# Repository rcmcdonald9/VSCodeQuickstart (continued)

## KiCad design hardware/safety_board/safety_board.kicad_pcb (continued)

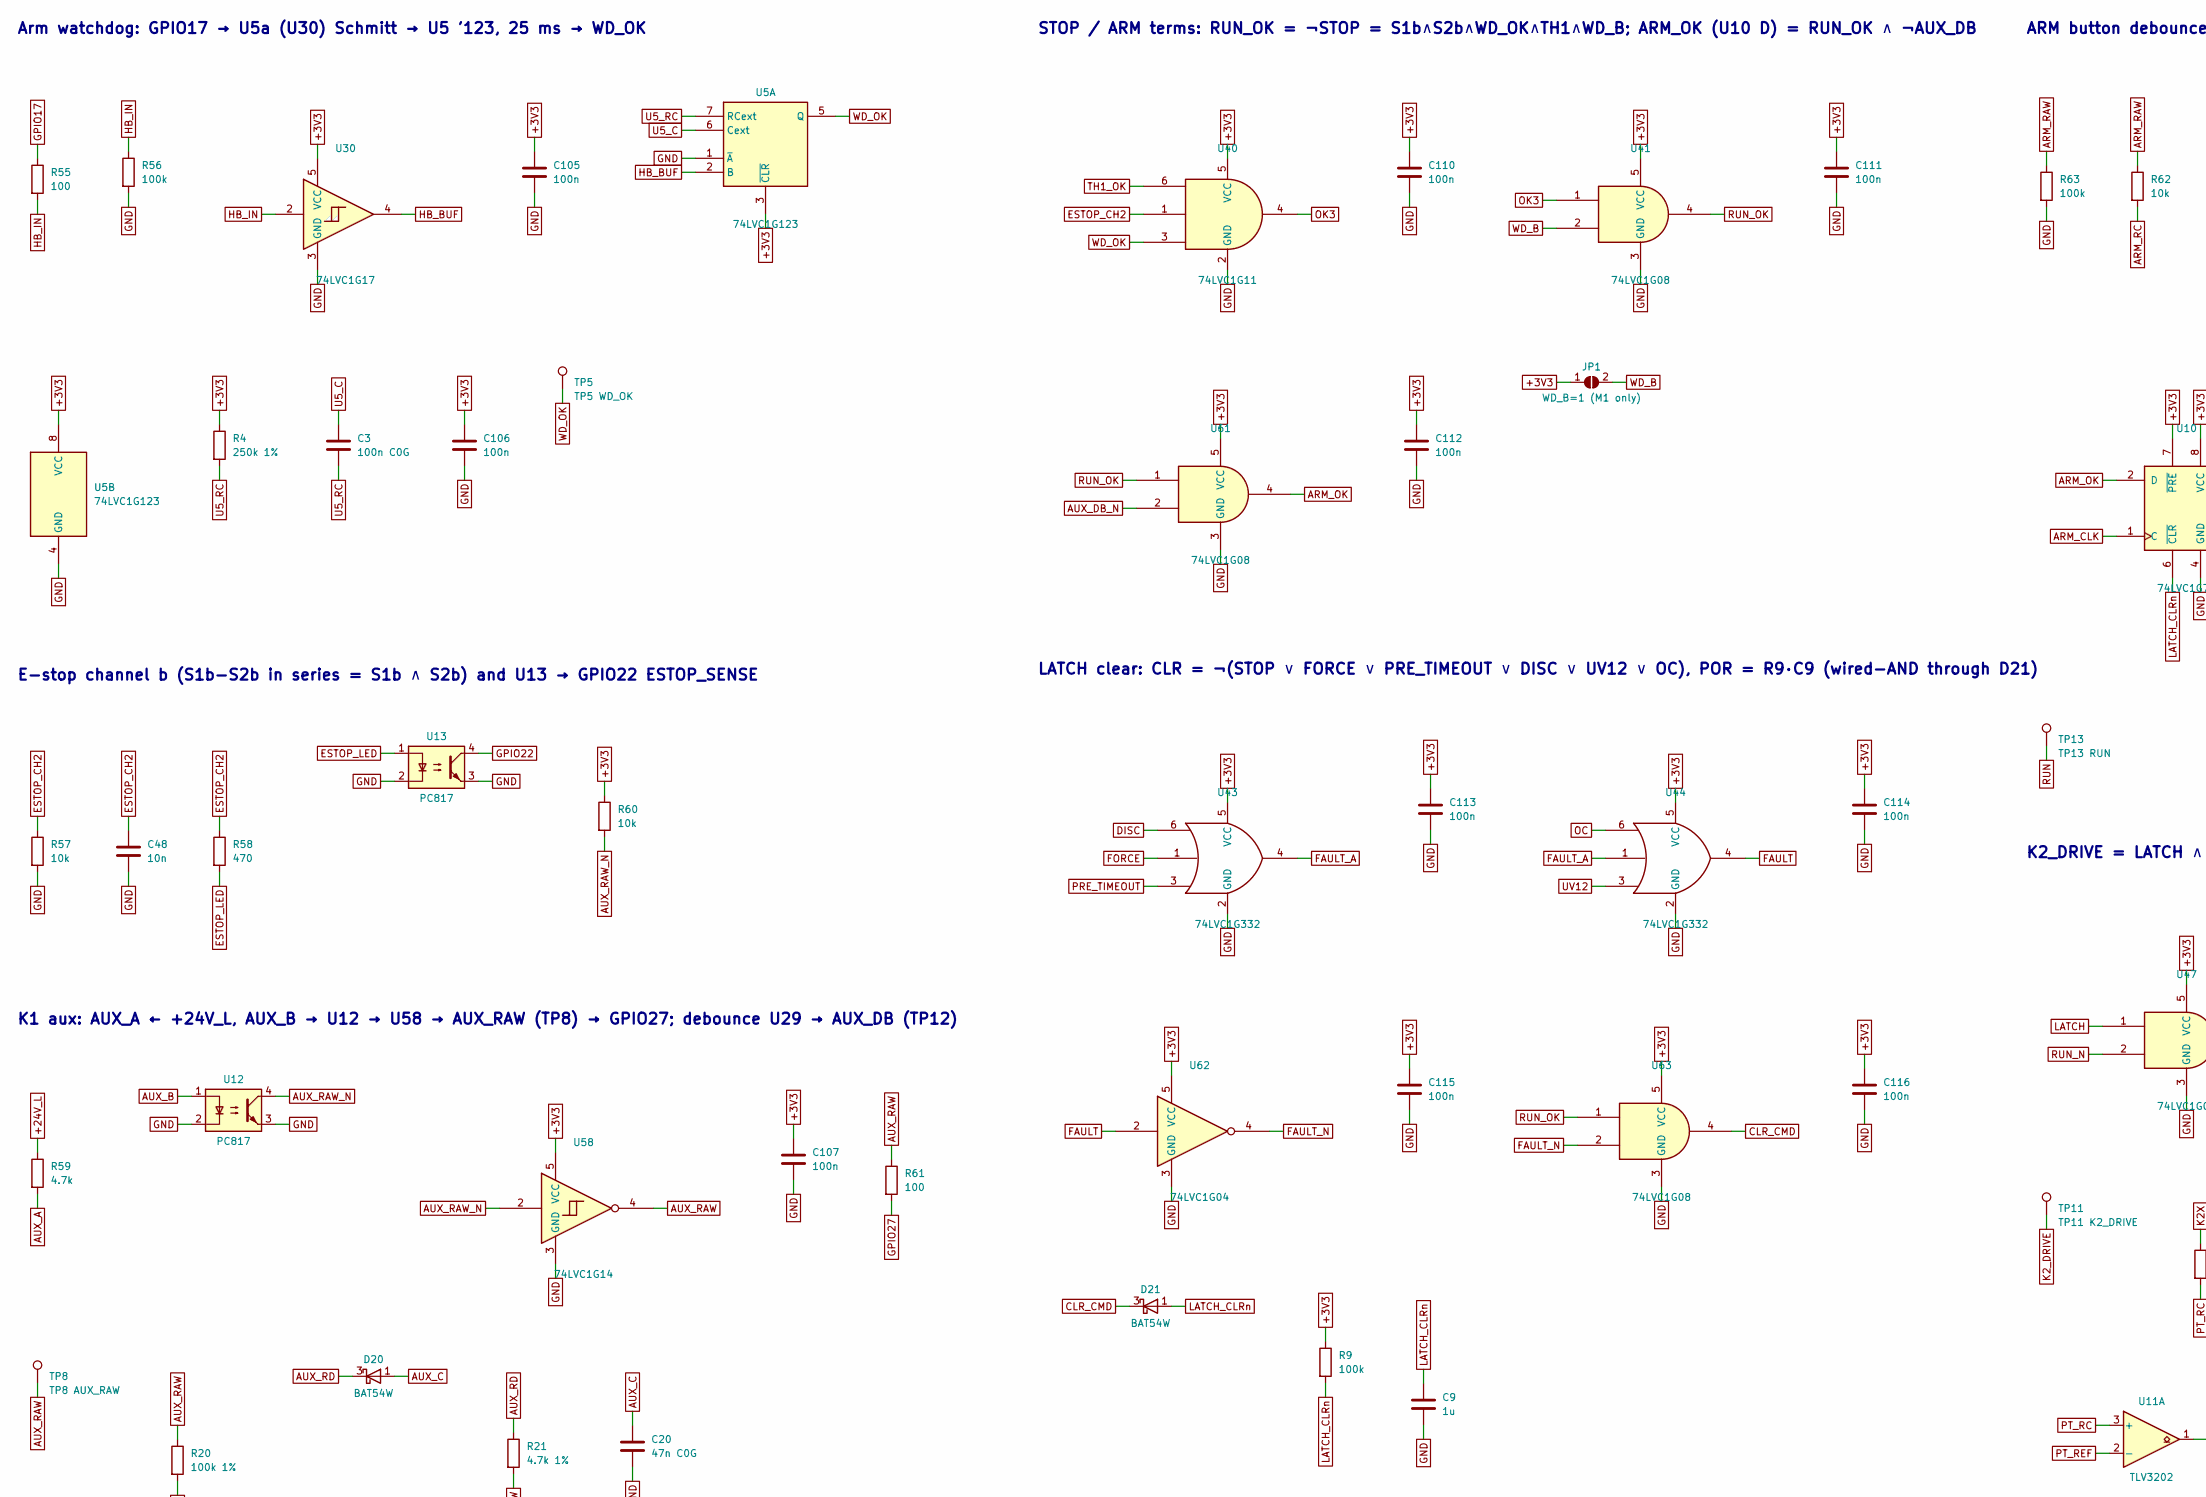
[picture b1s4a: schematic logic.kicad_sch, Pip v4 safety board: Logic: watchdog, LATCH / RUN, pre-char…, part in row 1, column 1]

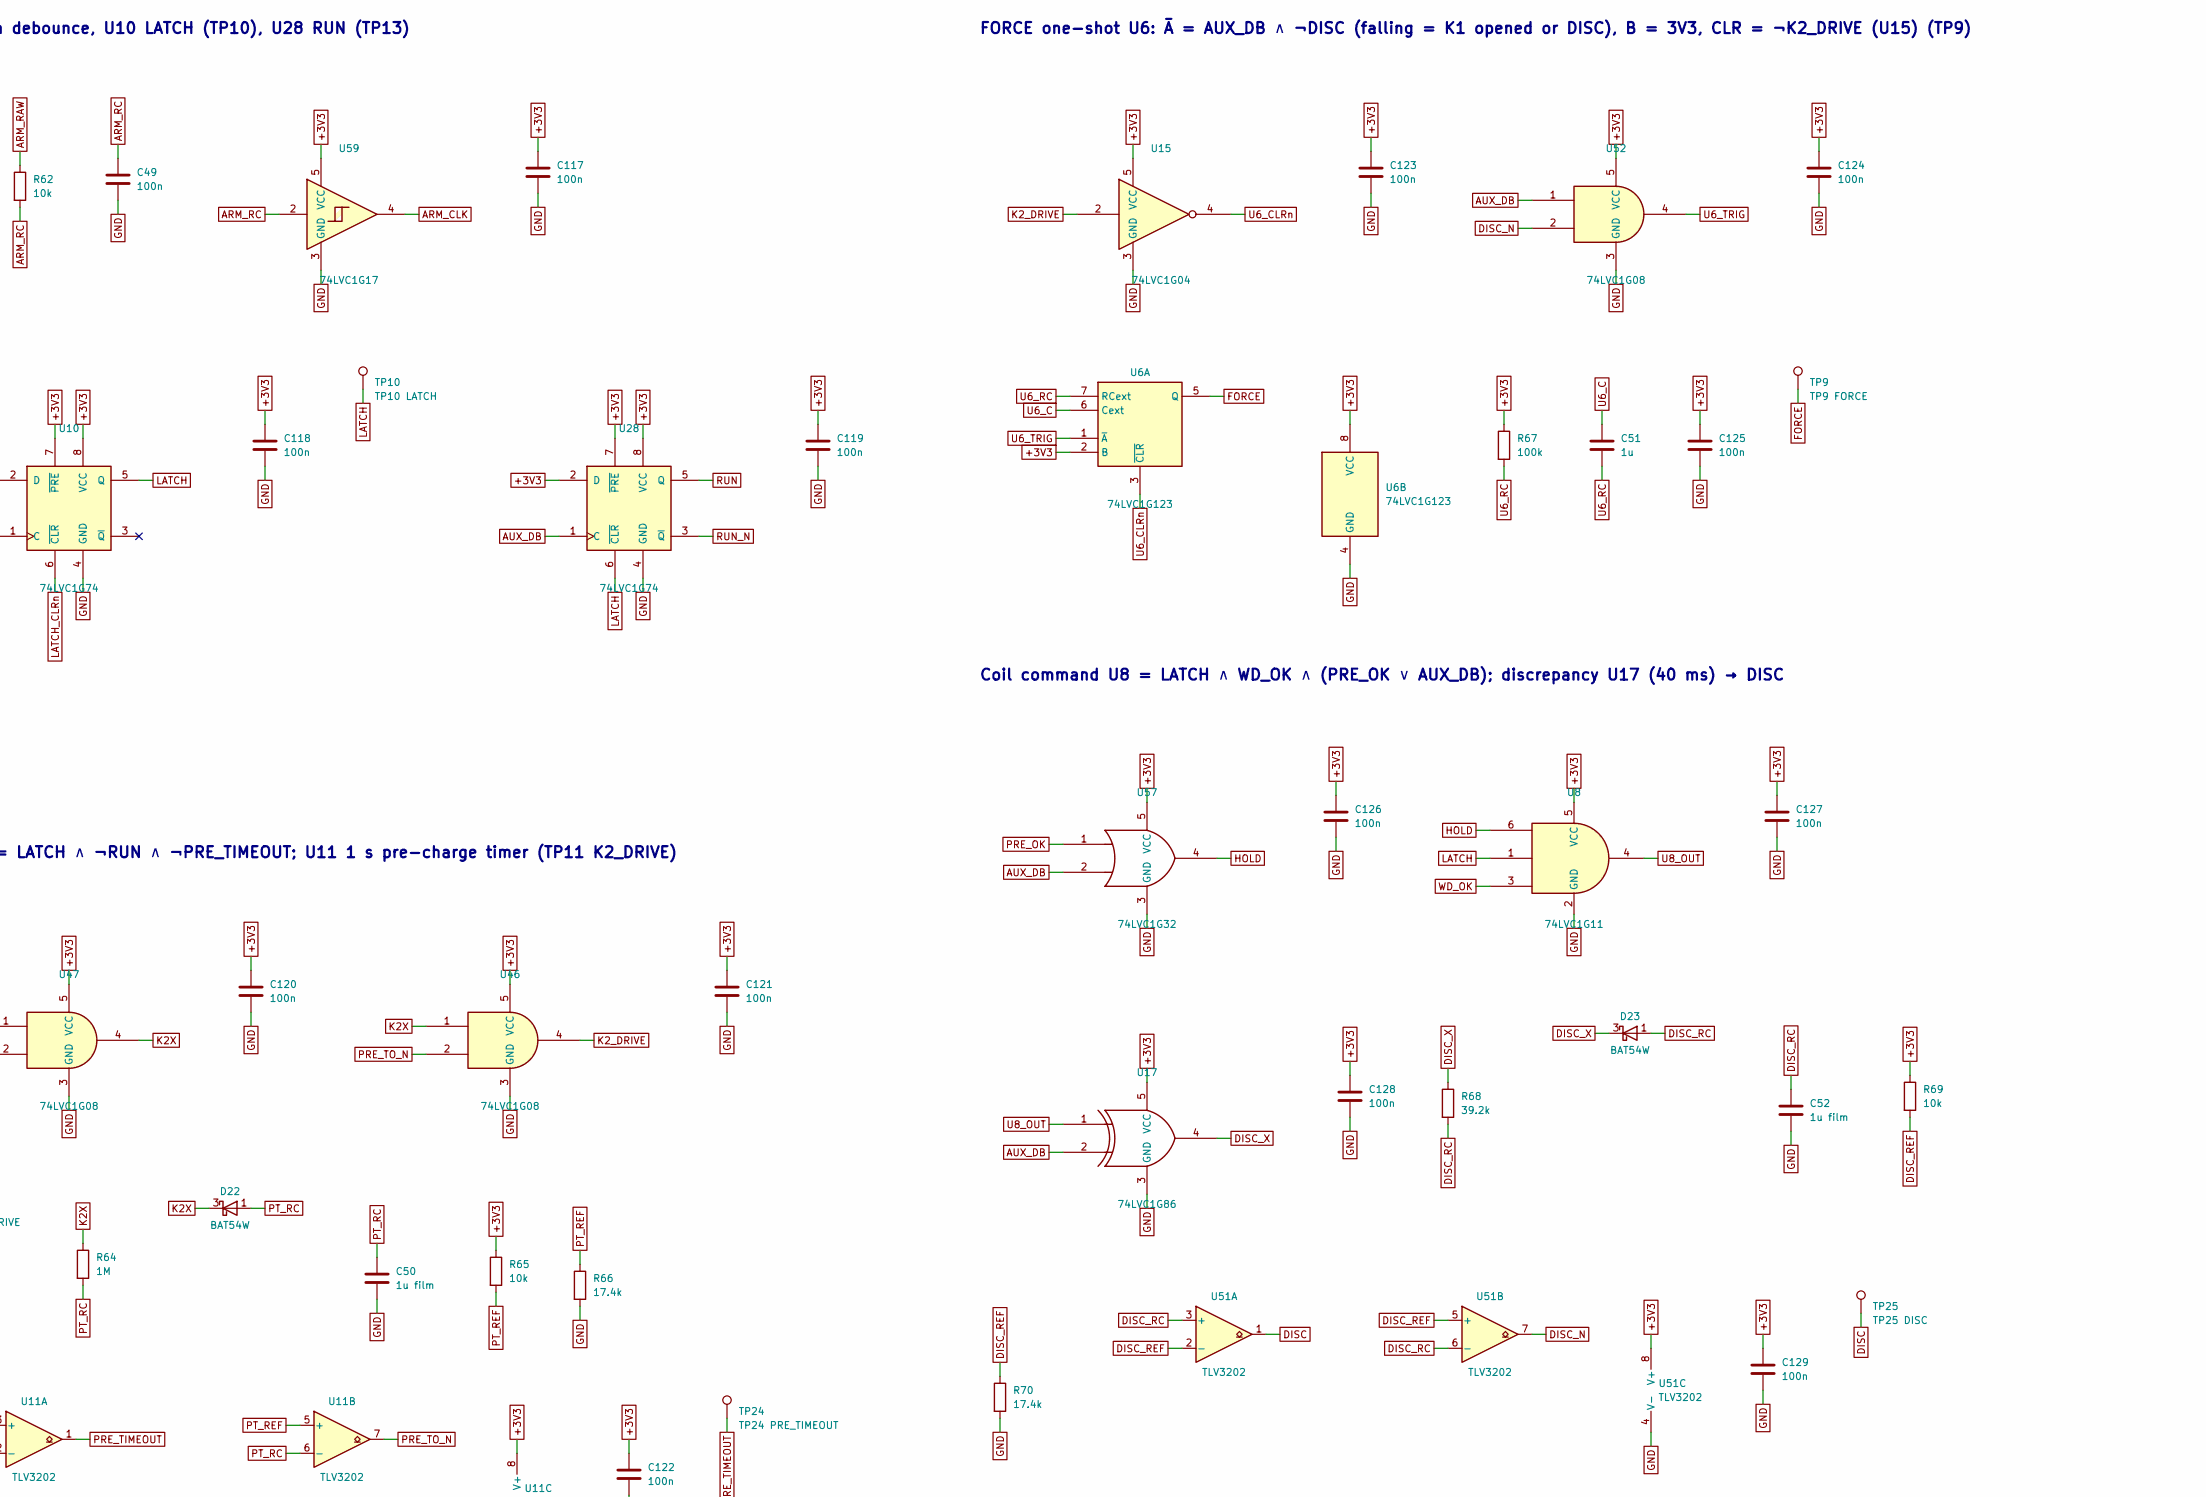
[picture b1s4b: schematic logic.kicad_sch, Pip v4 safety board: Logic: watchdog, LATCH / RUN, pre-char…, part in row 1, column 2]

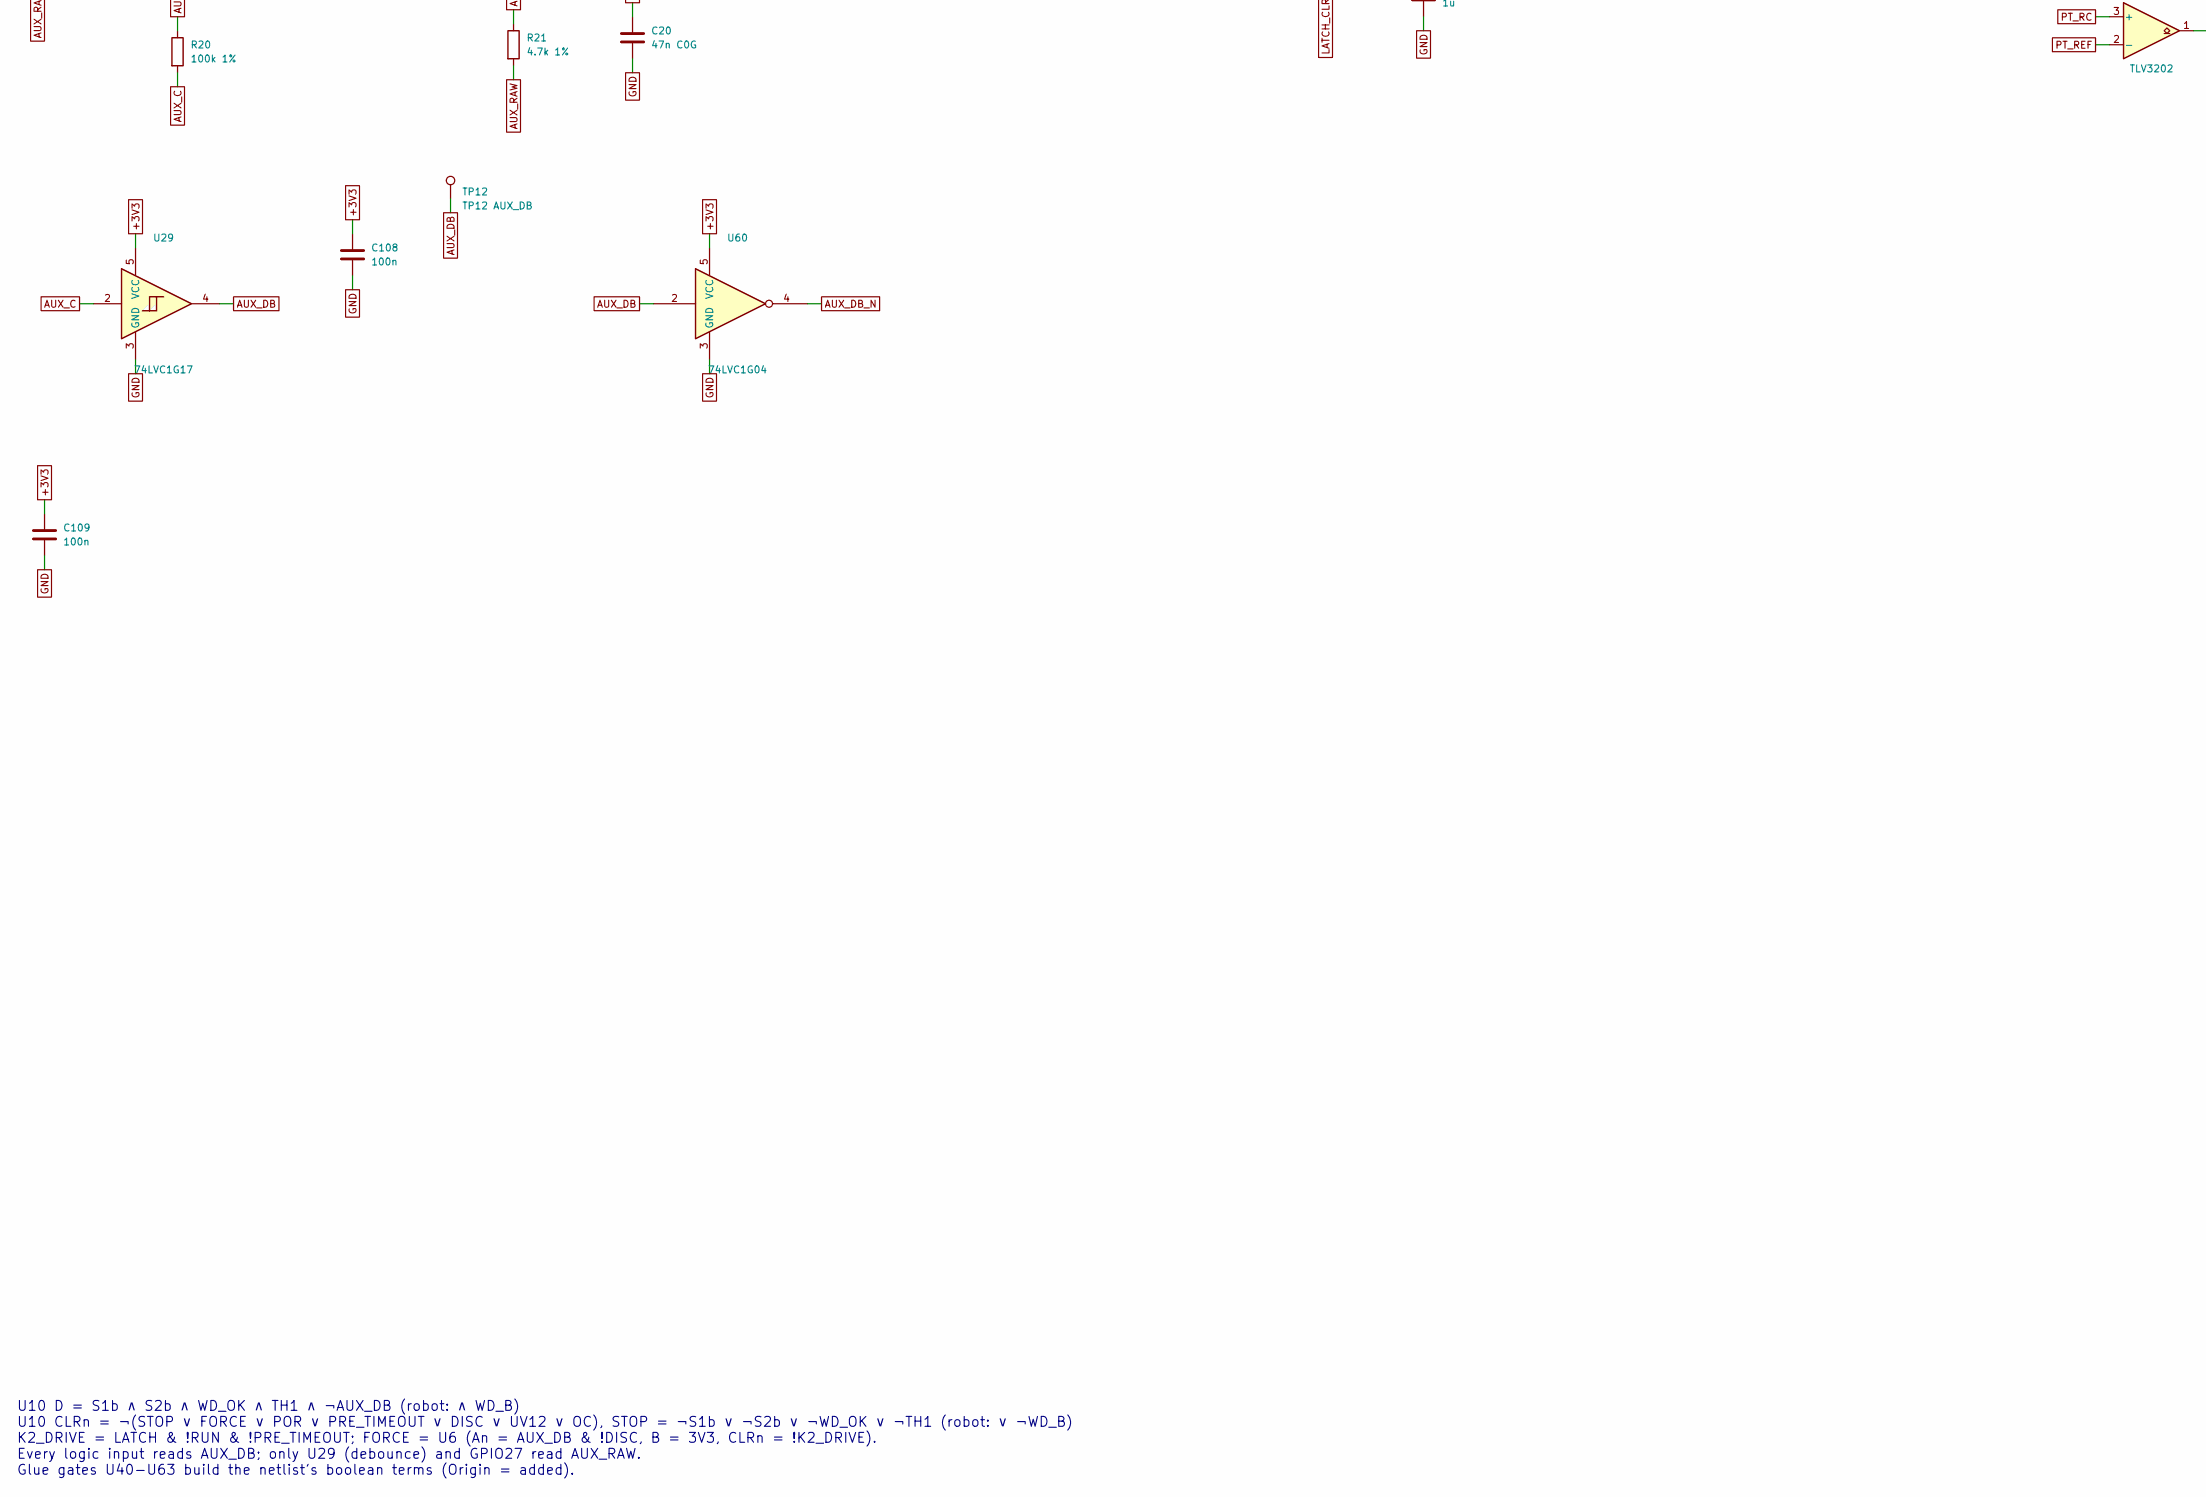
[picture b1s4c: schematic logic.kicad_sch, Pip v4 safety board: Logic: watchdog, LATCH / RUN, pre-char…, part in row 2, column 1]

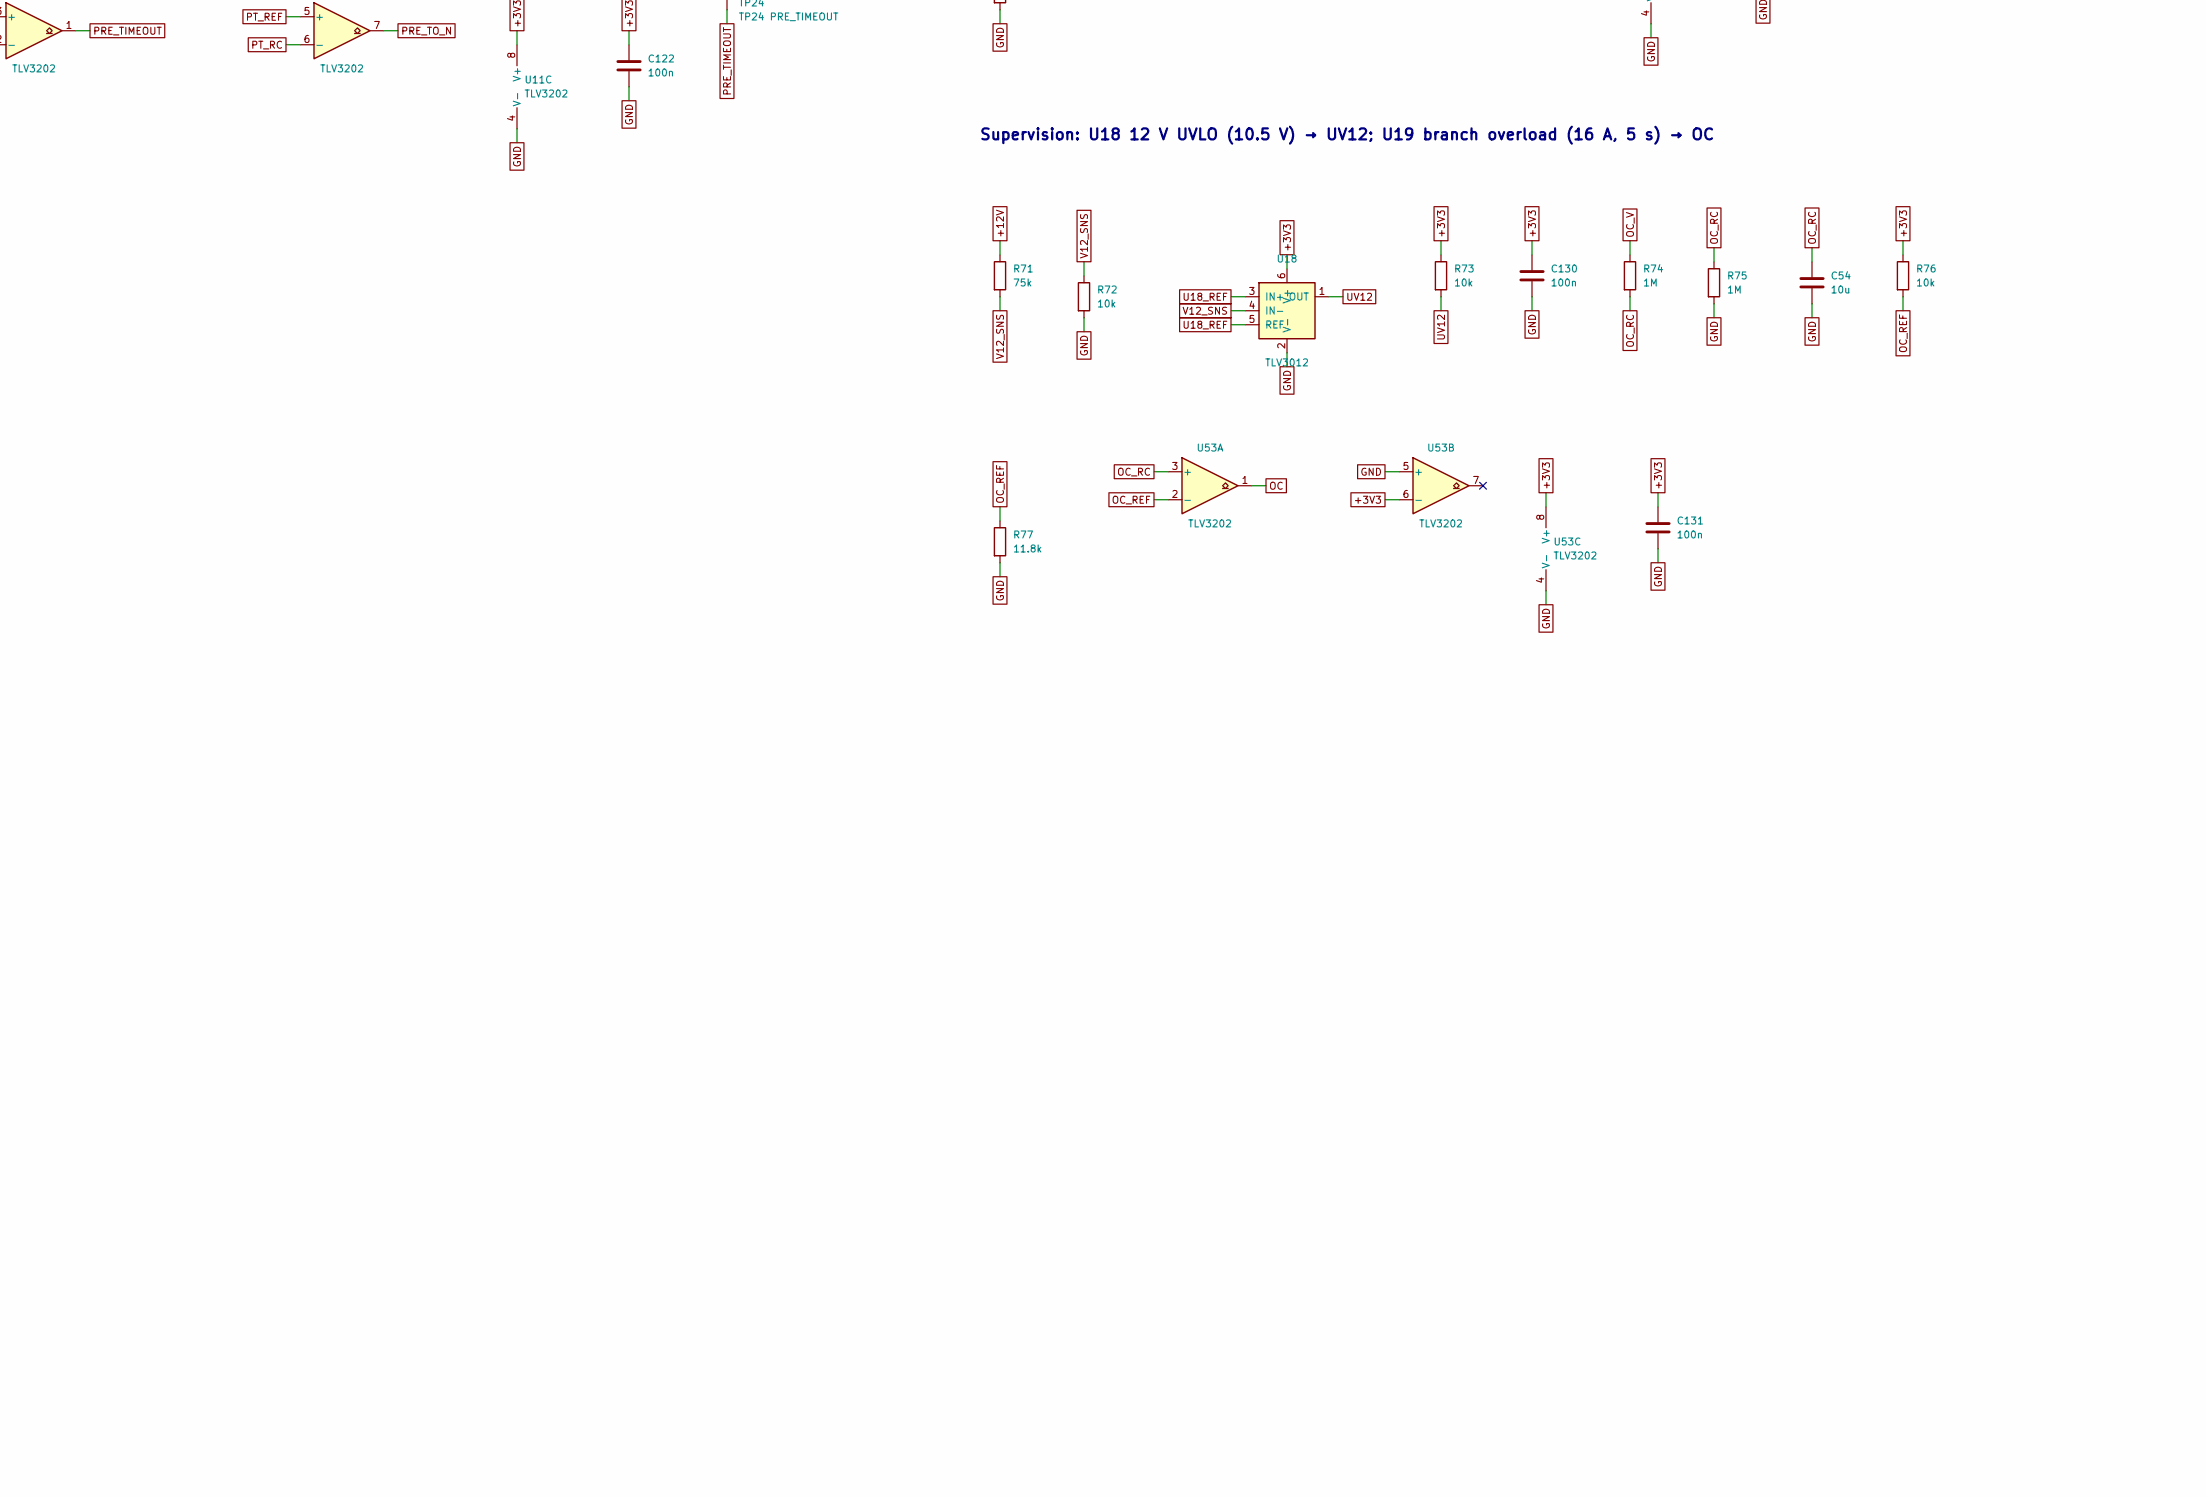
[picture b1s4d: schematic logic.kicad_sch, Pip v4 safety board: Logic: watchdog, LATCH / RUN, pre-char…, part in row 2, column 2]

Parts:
C3: 100n C0G; C_0603_1608Metric
C9, C51: 1u; C_1206_3216Metric
C20: 47n C0G; C_0603_1608Metric
C48: 10n; C_0603_1608Metric
C49, C105, C106, C107, C108, C109, C110, C111, C112, C113, C114, C115, C116, C117, C118, C119, C120, C121, C122, C123, C124, C125, C126, C127, C128, C129, C130, C131: 100n; C_0603_1608Metric
C50, C52: 1u film; C_1206_3216Metric
C54: 10u; C_1206_3216Metric
D20, D21, D22, D23: BAT54W; SOT-323_SC-70
JP1: WD_B=1 (M1 only); SolderJumper-2_P1.3mm_Open_RoundedPad1.0x1.5mm
R4: 250k 1%; R_0603_1608Metric
R9, R56, R63, R67: 100k; R_0603_1608Metric
R20: 100k 1%; R_0603_1608Metric
R21: 4.7k 1%; R_0603_1608Metric
R55, R61: 100; R_0603_1608Metric
R57, R60, R62, R65, R69, R72, R73, R76: 10k; R_0603_1608Metric
R58: 470; R_0603_1608Metric
R59: 4.7k; R_0603_1608Metric
R64, R74, R75: 1M; R_0603_1608Metric
R66, R70: 17.4k; R_0603_1608Metric
R68: 39.2k; R_0603_1608Metric
R71: 75k; R_0603_1608Metric
R77: 11.8k; R_0603_1608Metric
TP5: TP5 WD_OK; TestPoint_Keystone_5005-5009_Compact
TP8: TP8 AUX_RAW; TestPoint_Keystone_5005-5009_Compact
TP9: TP9 FORCE; TestPoint_Keystone_5005-5009_Compact
TP10: TP10 LATCH; TestPoint_Keystone_5005-5009_Compact
TP11: TP11 K2_DRIVE; TestPoint_Keystone_5005-5009_Compact
TP12: TP12 AUX_DB; TestPoint_Keystone_5005-5009_Compact
TP13: TP13 RUN; TestPoint_Keystone_5005-5009_Compact
TP24: TP24 PRE_TIMEOUT; TestPoint_Keystone_5005-5009_Compact
TP25: TP25 DISC; TestPoint_Keystone_5005-5009_Compact
U5, U6: 74LVC1G123; VSSOP-8_2.3x2mm_P0.5mm
U8, U40: 74LVC1G11; SOT-23-6
U10, U28: 74LVC1G74; VSSOP-8_2.3x2mm_P0.5mm
U11, U51, U53: TLV3202; SOIC-8_3.9x4.9mm_P1.27mm
U12, U13: PC817; DIP-4_W7.62mm
U15, U60, U62: 74LVC1G04; SOT-23-5
U17: 74LVC1G86; SOT-23-5
U18: TLV3012; SOT-23-6
U29, U30, U59: 74LVC1G17; SOT-23-5
U41, U46, U47, U52, U61, U63: 74LVC1G08; SOT-23-5
U43, U44: 74LVC1G332; SOT-23-6
U57: 74LVC1G32; SOT-23-5
U58: 74LVC1G14; SOT-23-5

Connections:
+3V3: C105.1, C106.1, C107.1, C108.1, C109.1, C110.1, C111.1, C112.1, C113.1, C114.1, C115.1, C116.1, C117.1, C118.1, C119.1, C120.1, C121.1, C122.1, C123.1, C124.1, C125.1, C126.1, C127.1, C128.1, C129.1, C130.1, C131.1, JP1.1 (A), R4.1, R9.1, R60.1, R65.1, R67.1, R69.1, R73.1, R76.1, U5.3 (~CLR), U5.8 (VCC), U6.2 (B), U6.8 (VCC), U8.5 (VCC), U10.7 (~PRE), U10.8 (VCC), U11.8 (V+), U15.5 (VCC), U17.5 (VCC), U18.6 (V+), U28.2 (D), U28.7 (~PRE), U28.8 (VCC), U29.5 (VCC), U30.5 (VCC), U40.5 (VCC), U41.5 (VCC), U43.5 (VCC), U44.5 (VCC), U46.5 (VCC), U47.5 (VCC), U51.8 (V+), U52.5 (VCC), U53.6 (-), U53.8 (V+), U57.5 (VCC), U58.5 (VCC), U59.5 (VCC), U60.5 (VCC), U61.5 (VCC), U62.5 (VCC), U63.5 (VCC); also elsewhere on the board
+12V: R71.1; also elsewhere on the board
+24V_L: R59.1; also elsewhere on the board
ARM_CLK: U10.1 (C), U59.4
ARM_OK: U10.2 (D), U61.4
ARM_RAW: R62.1, R63.1; also elsewhere on the board
ARM_RC: C49.1, R62.2, U59.2
AUX_A: R59.2; also elsewhere on the board
AUX_B: U12.1; also elsewhere on the board
AUX_C: C20.1, D20.1 (A), R20.2, U29.2
AUX_DB: TP12.1, U17.2, U28.1 (C), U29.4, U52.1, U57.2, U60.2
AUX_DB_N: U60.4, U61.2
AUX_RAW: R20.1, R21.2, R61.1, TP8.1, U58.4
AUX_RAW_N: R60.2, U12.4, U58.2
AUX_RD: D20.3 (K), R21.1
CLR_CMD: D21.3 (K), U63.4
DISC: TP25.1, U43.6, U51.1
DISC_N: U51.7, U52.2
DISC_RC: C52.1, D23.1 (A), R68.2, U51.3 (+), U51.6 (-)
DISC_REF: R69.2, R70.1, U51.2 (-), U51.5 (+)
DISC_X: D23.3 (K), R68.1, U17.4
ESTOP_CH2: C48.1, R57.1, R58.1, U40.1; also elsewhere on the board
ESTOP_LED: R58.2, U13.1
FAULT: U44.4, U62.2
FAULT_A: U43.4, U44.1
FAULT_N: U62.4, U63.2
FORCE: TP9.1, U6.5 (Q), U43.1; also elsewhere on the board
GND: C9.2, C20.2, C48.2, C49.2, C50.2, C52.2, C54.2, C105.2, C106.2, C107.2, C108.2, C109.2, C110.2, C111.2, C112.2, C113.2, C114.2, C115.2, C116.2, C117.2, C118.2, C119.2, C120.2, C121.2, C122.2, C123.2, C124.2, C125.2, C126.2, C127.2, C128.2, C129.2, C130.2, C131.2, R56.2, R57.2, R63.2, R66.2, R70.2, R72.2, R75.2, R77.2, U5.1 (~A), U5.4 (GND), U6.4 (GND), U8.2 (GND), U10.4 (GND), U11.4 (V-), U12.2, U12.3, U13.2, U13.3, U15.3 (GND), U17.3 (GND), U18.2 (V-), U28.4 (GND), U29.3 (GND), U30.3 (GND), U40.2 (GND), U41.3 (GND), U43.2 (GND), U44.2 (GND), U46.3 (GND), U47.3 (GND), U51.4 (V-), U52.3 (GND), U53.4 (V-), U53.5 (+), U57.3 (GND), U58.3 (GND), U59.3 (GND), U60.3 (GND), U61.3 (GND), U62.3 (GND), U63.3 (GND); also elsewhere on the board
GPIO17: R55.1; also elsewhere on the board
GPIO22: U13.4; also elsewhere on the board
GPIO27: R61.2; also elsewhere on the board
HB_BUF: U5.2 (B), U30.4
HB_IN: R55.2, R56.1, U30.2
HOLD: U8.6, U57.4
K2X: D22.3 (K), R64.1, U46.1, U47.4
K2_DRIVE: TP11.1, U15.2, U46.4; also elsewhere on the board
LATCH: TP10.1, U8.1, U10.5 (Q), U28.6 (~CLR), U47.1; also elsewhere on the board
LATCH_CLRn: C9.1, D21.1 (A), R9.2, U10.6 (~CLR)
OC: U44.6, U53.1
OC_RC: C54.1, R74.2, R75.1, U53.3 (+)
OC_REF: R76.2, R77.1, U53.2 (-)
OC_V: R74.1; also elsewhere on the board
OK3: U40.4, U41.1
PRE_OK: U57.1; also elsewhere on the board
PRE_TIMEOUT: TP24.1, U11.1, U43.3
PRE_TO_N: U11.7, U46.2
PT_RC: C50.1, D22.1 (A), R64.2, U11.3 (+), U11.6 (-)
PT_REF: R65.2, R66.1, U11.2 (-), U11.5 (+)
RUN: TP13.1, U28.5 (Q)
RUN_N: U28.3 (~Q), U47.2
RUN_OK: U41.4, U61.1, U63.1
TH1_OK: U40.6; also elsewhere on the board
U5_C: C3.1, U5.6 (Cext)
U5_RC: C3.2, R4.2, U5.7 (RCext)
U6_C: C51.1, U6.6 (Cext)
U6_CLRn: U6.3 (~CLR), U15.4
U6_RC: C51.2, R67.2, U6.7 (RCext)
U6_TRIG: U6.1 (~A), U52.4
U8_OUT: U8.4, U17.1; also elsewhere on the board
U18_REF: U18.3 (IN+), U18.5 (REF)
UV12: R73.2, U18.1 (OUT), U44.3
V12_SNS: R71.2, R72.1, U18.4 (IN-)
WD_B: JP1.2 (B), U41.2; also elsewhere on the board
WD_OK: TP5.1, U5.5 (Q), U8.3, U40.3

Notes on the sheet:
Arm watchdog: GPIO17 → U5a (U30) Schmitt → U5 '123, 25 ms → WD_OK
E-stop channel b (S1b-S2b in series = S1b ∧ S2b) and U13 → GPIO22 ESTOP_SENSE
K1 aux: AUX_A ← +24V_L, AUX_B → U12 → U58 → AUX_RAW (TP8) → GPIO27; debounce U29 → AUX_DB (TP12)
STOP / ARM terms: RUN_OK = ¬STOP = S1b∧S2b∧WD_OK∧TH1∧WD_B; ARM_OK (U10 D) = RUN_OK ∧ ¬AUX_DB
LATCH clear: CLR̄ = ¬(STOP ∨ FORCE ∨ PRE_TIMEOUT ∨ DISC ∨ UV12 ∨ OC), POR = R9·C9 (wired-AND through D21)
ARM button debounce, U10 LATCH (TP10), U28 RUN (TP13)
K2_DRIVE = LATCH ∧ ¬RUN ∧ ¬PRE_TIMEOUT; U11 1 s pre-charge timer (TP11 K2_DRIVE)
FORCE one-shot U6: Ā = AUX_DB ∧ ¬DISC (falling = K1 opened or DISC), B = 3V3, CLR̄ = ¬K2_DRIVE (U15) (TP9)
Coil command U8 = LATCH ∧ WD_OK ∧ (PRE_OK ∨ AUX_DB); discrepancy U17 (40 ms) → DISC
Supervision: U18 12 V UVLO (10.5 V) → UV12; U19 branch overload (16 A, 5 s) → OC
U10 D = S1b ∧ S2b ∧ WD_OK ∧ TH1 ∧ ¬AUX_DB (robot: ∧ WD_B) U10 CLRn = ¬(STOP ∨ FORCE ∨ POR ∨ PRE_TIMEOUT ∨ DISC ∨ UV12 ∨ OC), STOP = ¬S1b ∨ ¬S2b ∨ ¬WD_OK ∨ ¬TH1 (robot: ∨ ¬WD_B) K2_DRIVE = LATCH & !RUN & !PRE_TIMEOUT; FORCE = U6 (An = AUX_DB & !DISC, B = 3V3, CLRn = !K2_DRIVE). Every logic input rea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
